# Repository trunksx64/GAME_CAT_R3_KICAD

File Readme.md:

# Game//Cat ::: Revisión R3 :: Versión 3.50

## Razón de Ser e Inspiración

Este Control se basa en la Idea Original del Game//Cat Version R2, el cual a su vez se inspira en el diseño del joystick y botones del Arduino Esplora. El primer Control se implementó para ser usado como parametrizador y las siguientes revisiones se presentó como Tesis de Grado de Especialización de Instrumentación Industrial que curse. Se Utilizó principalmente como Herramienta de Programación para Tarjeta de Control de Ascensores Usando Un Firmware de Codito Cerrado. Se Implementó FREERTOS para su uso, así como librerías Básicas en MPLABX y XC16. La idea principal es utilizar los Microcontroladores de 16Bits de Microchip con periféricos listos y configurados. Es pequeño y Portable, ideal para llevar a todo lado, no intenta competir con controles similares a Arduino. Se desea implementar a futuro un Bootloader tanto por USB, RS232, SD y CAN.

Inicialmente, se Requiere un Programador Basado en PICKIT2/ICD3, MPLAB C30 Y MPLAB V4.0 como mínimo. 

En la Actualidad se recomienda el MPLAB SNAP, XC16 y MPLABX V6.0 

Algunos Elementos "Footprints" y "Symbols" están basados en mis librerías, cuáles encontrarán en este mismo Repositorio.

## Características del Hardware

  * Microcontrolador PIC24HJ128GP504.
  * Pantalla LCD PCD8544 (Based Nokia GLCD) - SPI.
  * Joystick Análogo de 2 ejes + Botón Digital.
  * 4 Botones Digitales.
  * Accelerometro - MMA8452Q - I2C. 
  * Sensor de Temperatura (LM61).
  * Sensor de Luz (LDR).
  * Memoria Eeprom 24LCXXX - I2C.
  * Memoria Ram 23KXX - SPI.
  * Ranura Memoria Micro-SD - SPI.
  * Buzzer por PWM.
  * Conexión USB - FTDI-RL232/UART - 5V.
  * Conexión CAN 5V.
  * 2 LED´s de Actividad.
  * Salidas Para PWM y UART - Con figurables - 3.3V.
  * Conexión ICSP con línea AUX, para control extra de puerto.
  * Cargador de Batería Lipo (MCP73831) con Indicador LED.

## Características Específicas

  * Debido a que el PIC trabaja a 3.3V, el uso del PCA82C251 y el FTDI-RL232 está a 5V, alimentado directamente por el Control USB, el FTDI-RL232 se encarga de "gestionar" la alimentación del sistema proporcionando un arranque suave en la tensión, luego se pasa por un regulador de 3,3V para alimentar el resto de componentes.
  * Para Potabilidad he agregado un control para la carga de Baterías de tipo Lipo, este gobernado él con el CI MCP73831, el cual mediante el uso del Mosfet DMP1045, intercambia la alimentación proveniente del FTDI-RL232 y la Batería según el estado de conexión USB, se puede usar Baterías de 3,7V en adelante hasta un máximo de 6V, cuando el Game//Cat está usando la Batería, el FTDI-RL232 se deshabilita.
  * Para el Manejo del Joystick, Botones, Sensor de Temperatura y Luz. He empleado el CI-74HC4051, que es un Multiplexor Análogo para leer los Valores por el módulo ADC, el cual puede utilizarse de 10 o 12Bits en conjunto con un canal DMA si fuere necesario.
  * La Comunicación UART, es una Salida/Entrada dedicada con un conversor de tensión de 3.3V a 5V de forma bidireccional con transistores Mosfet, con el fin de proteger y poder comunicar el PIC24H con cualquier tipo de dispositivo.
  * La Comunicación USB se hace por medio del CI FTDI-RL232, esto es porque el PIC no posee dicho Módulo y además permite ahorrar en la Memoria del PIC el Stack del USB, esto permite que sea Conectar y Usar, puesto que los Drives de este USB son reconocidos de forma inmediata por Windows y Linux sin problemas.
  * La Comunicación CAN la he Incluido porque en estos momentos trabajo con esta interfase y su popularidad ha crecido bastante, por experiencia este BUS es muy robusto y fácil de usar, en el PIC se hace uso de dos canales DMA teniendo una respuesta bastante rápida y sin sacrificar la memoria RAM principal, su conexión se hace por medio del Transeiver PCA82C251, además he agregado un par de diodos TVH para proteger dicho CI.
  * La Ranura para la Tarjeta Micro-SD, posee conexión con el Módulo SPI, el cual está compartida con la Memoria Ram 23Kxxx, Además la pantalla posee también una conexión al segundo Módulo SPI, que puede usarse para "colgar" otros dispositivos si no vamos a usar la Pantalla.
  * El control del Buzzer se ha dejado por un Pin que puede ser utilizado tanto por el módulo PWM o un pin Común, su uso dependerá del Programa o Aplicación.
  * Posee una Memoria I2C en conjunto con un Accelerometro, con comunicación directa.
  * La programación se hace por medio de la conexión ICSP o Bootloader por USB, usando cualquier programador, PICKIT2-3 y/ó ICD2-3, igual estas salidas pueden usarse como cualquier puerto, teniendo presente que no poseen ninguna protección a tensiones superiores de 3,3V.
  * Ya por Último, he dejado dos visualiza-dores, que son libres de uso.

Básicamente, esto es el GAME//CAT, una tarjeta más que un sistema de control para usuarios avanzados, es una tarjeta de entrenamiento para los principiantes, puesto que todo lo que incluye hace uso forzoso de todo los controles que el PIC24HJ128GP504 incorpora.

## Microcontrolador

* Architecture 16-bit.
* CPU Speed Max. 40 MIPS.
* Memory Type Flash.
* Program Memory 128Kb.
* RAM 8,192 Bytes.
* Temperature Range C -40 to 150.
* Operating Voltage Range (V) 3 to 3.6.
* I/O Pins 35 & Pin Count 44.
* Internal Oscillator 7.37 MHz, 32.768 kH.
* Digital Communication Peripherals 2-UART, 2-SPI,1-I2C, 1-CAN.
* Comparators 2, Capture/Compare/PWM Peripherals 4/4, PWM Resolution bits 16.
* Timers 5 x 16-bit 2 x 32-bit.
* Parallel Port PMP(No Usado), Hardware RTCC-1 (No Usado).
* Chanel DMA-8.
* Cap Touch Channels-13 (No Usado).

## Versiones

* 2017 : 1.0.0 : Primera Versión en Kicad 4
* 2017 : 1.2.0 : Se Agregó Conversión de Tensión 5V a 3.3V Bidireccional en salida UART y PWM, se eliminó conexión DC externa.
* 2018 : 2.0.0 : Se Migró completamente a Kicad 5, el Led control se removió para dar opción de selección de Periférico SPI (Ram y SD).
* 2018 : 2.1.0 : Se rediseñó y corrigió error en botón del Joystick, se corrigió el trucado de líneas de Programación PGM y PGD.
* 2018 : 2.2.0 : Se Agregó Resistencias de protección (0Ohm) en entradas Jack RJ11 de Programación.
* 2018 : 2.1.0 : Se Agregó y Calibro Resistencia del Botón de Reset, se agregó control se Carga para Bateria Lipo 3.3V.
* 2018 : 2.5.0 : Se Actulizaron Logos de la Marca y de Hardware Libre, se Actualizó a licencia Creative Commons V4.
* 2018 : 2.7.0 : Se Actualizaron las Librerías de Módulos de Kicad, basadas en Progetti Walter.
* 2018 : 2.9.0 : Se Agregaron condensadores de filtrado al multiplexor análogo, se cambiaron los botones por diseño con poste.
* 2019 : 2.9.1 : Se Organizaron los Archivos para Hospedarlos en Github, Se Ordenaron condensadores y Cristal del PIC.
* 2021 : 2.9.1 : Se Actualiza a KiCad 6 todos los archivos y Librerías.
* 2022 : 3.0.0 : Se Actualizaron los Valores de las resistencias del conversor de 5V-3.3V de un 1K a 10K.
* 2022 : 3.1.0 : Se reestructuró completamente los esquemáticos y se usaron páginas separadas para cada Módulo.
* 2022 : 3.2.0 : Se corrigieron errores en los anchos de pista y reubicaron varios elementos como Seregrafia.
* 2022 : 3.3.0 : Se Actualizaron los conectores Moles para cuatros Salidas, sumando VCC y GND para alimentar controles externos.
* 2022 : 3.5.0 : Se Actualizaron los Logos y posiciones de Seregrafia de Varios componentes.

## ERRATAS

* Debido a tolerancia de tensión del MCP2551, no es posible usarlo para tensiones de 3.3V, cuál hacer imposible usar el CANBUS, sé recomienda usar el PCA82C251 cuál soportar desde 1.8V hasta 24V.

## Créditos

xDNA Electronics & Desing es una microempresa Personal, que se dedica y encarga de elaborar proyectos de Control y Automatización por pedido, su idea es colaborar y ayudar a quines a si lo requieran, el proyecto se hizo principalmente como Hobby el cual gracias a terceros se pudo implementar y hacer su creación, por lo cual se da la libertad de usarlo para experimentar sin hacer uso comercial del mismo.

## Licencia

Licensed under Attribution-NonCommercial-ShareAlike 4.0 International (CC BY-NC-SA 4.0)

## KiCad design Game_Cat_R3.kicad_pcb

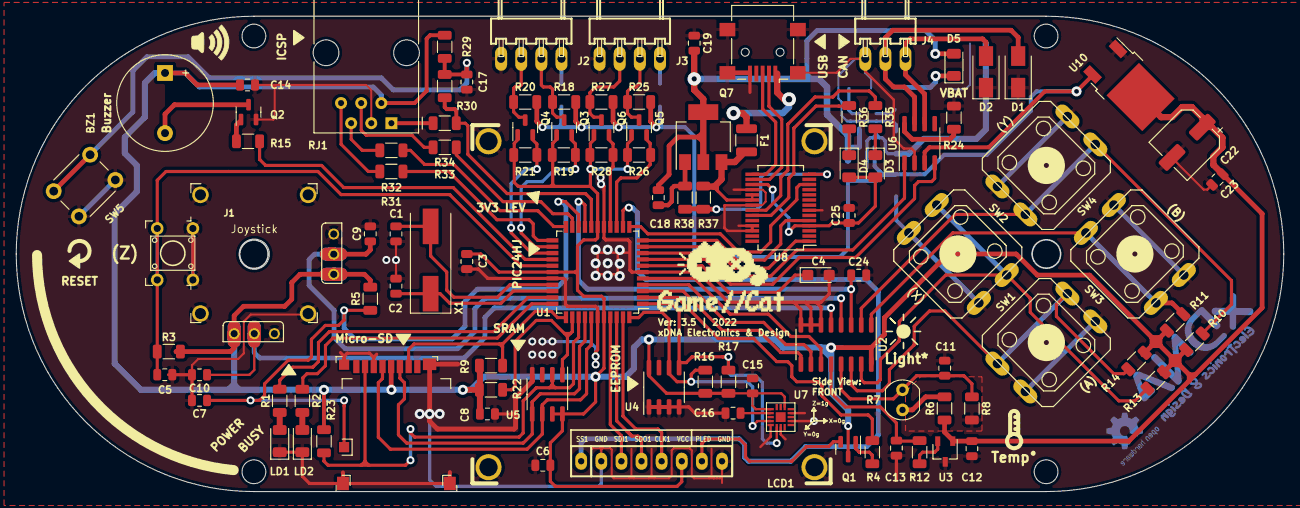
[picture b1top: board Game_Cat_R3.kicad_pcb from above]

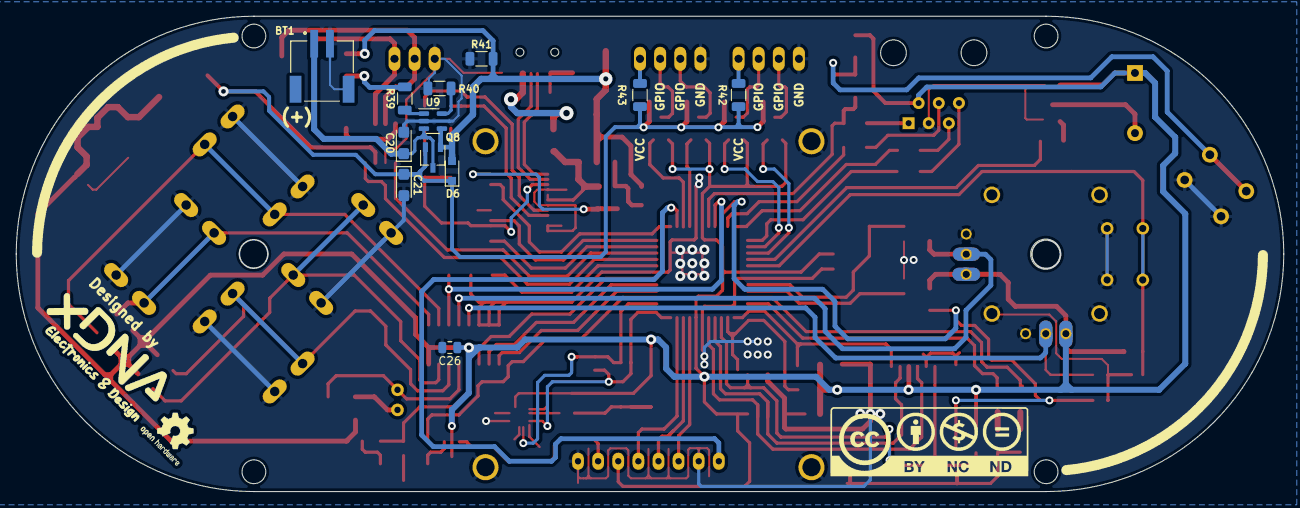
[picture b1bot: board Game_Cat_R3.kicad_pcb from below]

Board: 2 copper layers, 160.0 x 60.0 mm, 113 parts (12 on the bottom side), 87 nets.

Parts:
BT1: 3V7; Connector_1x02_P2.0mm
BZ1: Buzzer; Buzzer_12x9.5RM7.6
C1, C2: 22pF; C_0805_2012Metric
C3, C25: 100uF; C_0805_2012Metric
C4: 10uF; CP_EIA-3216-18_Kemet-A
C5, C7, C9, C10, C24, C26: 10pF; C_0805_2012Metric
C6, C8, C11, C12, C14, C15, C16: 10nF; C_0805_2012Metric
C13, C17, C18, C19, C23: 100nF; C_0805_2012Metric
C20: 4.7uF; CP_EIA-3216-18_Kemet-A
C21: 1uF; CP_EIA-3216-18_Kemet-A
C22: 100uF; CP_Elec_6.3x4.5
D1, D2: D_TVS; D_SMA
D3, D4: LED; LED_1206_3216Metric
D5: VBAT; LED_1206_3216Metric
D6: BAT60J; D_SOD-323_HandSoldering
F1: Fuse; R_1210_3225Metric
J1: Joystick; JOYSTICK_TUMB
J2: UART; MOLEX_KK_1x04_P2.54mm_HORIZONTAL
J3: PWM; MOLEX_KK_1x04_P2.54mm_HORIZONTAL
J4: CAN; MOLEX_KK_1x03_P2.54mm_HORIZONTAL
LCD1: PCD8544-BASE; GLCD_PCD8544_BASE
LD1: POWER; LED_1206_3216Metric
LD2: BUSY; LED_1206_3216Metric
Q1: MMBT3906; SOT-23
Q2: MMBT3904; SOT-23
Q3, Q4, Q5, Q6: BSS138; SOT-23
Q7: IRFL901; SOT-223
Q8: NTR1P02LT1G; TSOT-23
R1, R2, R35: 330R; R_1206_3216Metric
R3, R4, R5, R6, R8, R10, R11, R12, R13, R14, R18, R19, R20, R21, R25, R27, R28, R29, R37, R40: 10K; R_1206_3216Metric
R7: VT93xx; R_LDR_4.9x4.2mm_P2.54mm_Vertical
R9, R15, R22, R23, R24, R26, R38, R42, R43: 1K; R_1206_3216Metric
R16, R17: 4K7; R_1206_3216Metric
R30, R39: 470R; R_1206_3216Metric
R31, R32, R33, R34: 0R; R_1206_3216Metric
R36: 33OR; R_1206_3216Metric
R41: 100K; R_1206_3216Metric
RJ1: RJ12; RJ12_Horizontal
Ref**: GameCatPixel; xdna_game_cat_logo_skill_pixel
SD1: Micro-SD; MICRO_SD_HC_DM3AT
SW1: (A); SW_PUSH_PTS_125x12mm_SNAP_GREEN
SW2: (X); SW_PUSH_PTS_125x12mm_SNAP_BLUE
SW3: (B); SW_PUSH_PTS_125x12mm_SNAP_RED
SW4: (Y); SW_PUSH_PTS_125x12mm_SNAP_YELLOW
SW5: RESET; SW_PUSH_6mm_H5mm
U1: PIC24HJXXXGPX04_TQFP; TQFP-44_10x10mm_P0.8mm
U2: 74HC4051; SOIC-16_3.9x9.9mm_P1.27mm
U3: LM61; TSOT-23
U4: M24C512; SOIC-8_3.9x4.9mm_P1.27mm
U5: 23KXX; SOIC-8_3.9x4.9mm_P1.27mm
U6: PCA82C251; SOIC-8_3.9x4.9mm_P1.27mm
U7: MMA8452Q; QFN_16_3x3x1mm_P0.5mm
U8: FT232RL; SSOP-28_5.3x10.2mm_P0.65mm
U9: MCP73831; SOT-23-5
U10: LM1117; TO-252-2
USB1: USB_B_Micro; USB_Mini-B_Lumberg_2486_01_Horizontal
X1: 4Mhz; Crystal_SMD_HC49-SD

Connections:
+3.3VA: D3.2 (A), D4.2 (A), U8.4 (VCCIO), U8.17 (3V3OUT)
+3V3: BZ1.1 (-), C3.1, C6.1, C8.1, C12.1, C14.1, C15.1, C22.1, C23.2, C26.1, J1.1 (V+), J1.4 (H+~), LCD1.6 (VCC), Q1.3 (C), Q3.1 (G), Q4.1 (G), Q5.1 (G), Q6.1 (G), R3.2, R5.2, R6.1, R9.1, R10.1, R11.1, R13.1, R14.1, R16.1, R17.1, R19.2, R21.2, R22.1, R23.1, R26.2, R28.2, R29.2, RJ1.2, SD1.4 (VDD), U1.17 (AVDD), U1.28 (VDD), U1.40 (VDD), U2.16 (VCC), U3.1 (VCC), U4.8 (VCC), U5.7 (HOLD), U5.8 (VDD), U7.1 (VDDIO), U7.14 (VDD), U10.2 (VO)
+5C: C21.1, D6.1 (K), Q8.2 (S), R18.1, R20.1, R25.1, R27.1, R42.1, R43.1, U6.3 (VCC), U10.3 (VI)
+5V: F1.2, Q7.3 (S), R37.2, U8.19 (~RESET), U8.20 (VCC)
/BUTTONS/Axis(X): C10.1, J1.2 (V), U2.5 (A5)
/BUTTONS/Axis(Y): C9.1, J1.5 (H), U2.4 (A7)
/BUTTONS/Button(A): R14.2, SW1.1, SW1.2, U2.14 (A1)
/BUTTONS/Button(B): R11.2, SW3.1, SW3.2, U2.1 (A4)
/BUTTONS/Button(X): R13.2, SW2.1, SW2.2, U2.15 (A2)
/BUTTONS/Button(Y): R10.2, SW4.1, SW4.2, U2.2 (A6)
/BUTTONS/CANH: D1.2 (A2), J4.2, U6.7 (CAN+)
/BUTTONS/CANL: D2.2 (A2), J4.1, U6.6 (CAN-)
/BUTTONS/Light: C11.1, R7.2, R8.1, U2.13 (A0)
/BUTTONS/Temp: C13.2, R12.1, U2.12 (A3)
/MICROCONTROLLER/VCAP: C4.1, U1.7 (VCAP)
/POWER_SUPPLY/BAT: BT1.1 (+), C20.1, Q8.3 (D), U9.3 (VBAT)
/POWER_SUPPLY/CBUS0: R36.1, U8.23 (CBUS0)
/POWER_SUPPLY/CBUS1: R35.1, U8.22 (CBUS1)
/POWER_SUPPLY/PWREN: R37.1, R38.2, U8.14 (CBUS3)
ADC-IN: C24.1, U1.19 (RA0/CN2/VREF+/AN0), U2.3 (A)
AUX_ICD: R31.2, U1.23 (AN4/C1IN-/RP2/CN6/RB2)
BUTTON_Z: C5.1, J1.7 (B+), R3.1, U1.27 (RC2/CN10/PMA2/RP18/CVREF/AN8)
BUZZER: R15.1, U1.26 (RC1/CN9/RP17/AN7)
CHECK-SD: C7.1, R5.1, U1.20 (RA1/CN3/VREF-/AN1)
GLCD_LED: R4.1, U1.2 (RC6/PMA1/CN18/RP22)
GND: BT1.2 (-), C1.2, C2.1, C3.2, C4.2, C5.2, C6.2, C7.2, C8.2, C9.2, C10.2, C11.2, C12.2, C13.1, C14.2, C15.2, C16.2, C17.1, C19.1, C20.2, C21.2, C22.2, C23.1, C24.2, C25.2, C26.2, D1.1 (A1), D2.1 (A1), J1.3 (V-), J1.6 (H-), J1.8 (B-), J1.9 (SHIELD), J2.4, J3.4, J4.3, LCD1.2 (SCE), LCD1.8 (GND), LD1.1 (K), LD2.1 (K), Q2.2 (E), R8.2, R24.1, R40.1, R41.1, RJ1.3, SD1.6 (VSS), SW1.3 (K), SW1.4 (A), SW2.3 (K), SW2.4 (A), SW3.3 (K), SW3.4 (A), SW4.3 (K), SW4.4 (A), SW5.1, U1.6 (VSS), U1.16 (AVSS), U1.29 (VSS), U1.39 (VSS), U2.6 (~E), U2.7 (VEE), U2.8 (GND), U3.3 (GND), U4.1 (E0), U4.2 (E1), U4.3 (E2), U4.4 (VSS), U4.7 (~WC), U5.4 (VSS), U6.2 (GND), U7.5 (GND), U7.7 (SAO), U7.10 (GND), U7.12 (GND), U8.7 (GND), U8.18 (GND), U8.21 (GND), U8.25 (AGND), U8.26 (TEST), U9.2 (VSS), U10.1 (GND), USB1.5 (GND), USB1.6 (Shield)
I2C_SCL: R16.2, U1.44 (SCL1/RP8/CN22/PMD4/RB8), U4.6 (SCL), U7.4 (SCL)
I2C_SDA: R17.2, U1.1 (SDA1/RP9/CN21/PMD3/RB9), U4.5 (SDA), U7.6 (SDA)
MISO_GLCD: LCD1.3 (DC), U1.41 (PGED3/ASDA1/RP5/CN27/PMD7/RB5)
MISO_MEN: R23.2, SD1.7 (DO), U1.36 (RC3/PMBE/CN28/RP19), U5.2 (SO)
MOSI_GLCD: LCD1.4 (DIN), U1.42 (PGEC3/ASCL1/RP6/CN24/PMD6/RB6)
MOSI_MEN: SD1.3 (DI), U1.37 (RC4/PMA4/CN25/RP20), U5.5 (SI)
MUX_A: U1.5 (RC9/PMA6/CN19/RP25), U2.11 (S0)
MUX_B: U1.4 (RC8/PMA5/CN20/RP24), U2.10 (S1)
MUX_C: U1.3 (RC7/CN17/PMA0/RP23), U2.9 (S2)
unnamed: BZ1.2 (+), Q2.3 (C)
unnamed: C1.1, U1.30 (RA2/CN30/CLKI/OSC1), X1.2
unnamed: C2.2, U1.31 (RA3/CN29/CLKO/OSC2), X1.1
unnamed: C16.1, U7.2 (BYP)
unnamed: C17.2, R29.1, R30.1, SW5.2
unnamed: C18.1, C19.2, D5.2 (A), D6.2 (A), Q7.2 (D), Q8.1 (G), R41.2, U9.4 (VDD)
unnamed: C18.2, Q7.1 (G), R38.1
unnamed: D3.1 (K), R35.2
unnamed: D4.1 (K), R36.2
unnamed: D5.1 (K), R39.2
unnamed: F1.1, USB1.1 (VBUS)
unnamed: J2.1, R42.2
unnamed: J2.2, Q3.3 (D), R18.2
unnamed: J2.3, Q4.3 (D), R20.2
unnamed: J3.1, R43.2
unnamed: J3.2, Q5.3 (D), R25.2
unnamed: J3.3, Q6.3 (D), R27.2
unnamed: LCD1.7 (LED), Q1.2 (E)
unnamed: LD1.2 (A), R1.2
unnamed: LD2.2 (A), R2.2
unnamed: Q1.1 (B), R4.2
unnamed: Q2.1 (B), R15.2
unnamed: R1.1, U1.32 (RA8/PMA8/TDO)
unnamed: R2.1, U1.33 (SOSCI/RP4/CN1/RB4)
unnamed: R6.2, R7.1
unnamed: R12.2, U3.2 (Vo)
unnamed: R24.2, U6.8 (Rsl)
unnamed: R31.1, RJ1.6
unnamed: R32.1, RJ1.5
unnamed: R33.1, RJ1.4
unnamed: R34.1, RJ1.1
unnamed: R39.1, U9.1 (STAT)
unnamed: R40.2, U9.5 (PROG)
unnamed: U8.15 (USBD+), USB1.3 (D+)
unnamed: U8.16 (USBD-), USB1.2 (D-)
PGC_ICD: R32.2, U1.22 (PGEC1/AN3/C2IN+/RP1/CN5/RB1)
PGD_ICD: R33.2, U1.21 (PGED1/AN2/C2IN-/RP0/CN4/RB0)
RESET_CTRL: R30.2, R34.2, U1.18 (MCLR)
RX_CAN: U1.8 (PGED2/EMCD2/RP10/CN16/PMD2/RB10), U6.4 (RxD)
RX_UART_A: Q4.2 (S), R21.1, U1.25 (RC0/CN8/RP16/AN6)
RX_UART_B: Q6.2 (S), R28.1, U1.15 (AN9/RP15/CN11/PMCS1/RB15)
RX_USB: U1.10 (AN12/RP12/CN14/PMD0/RB12), U8.1 (TXD)
SCK_GLCD: LCD1.5 (CLK), U1.43 (INT0/RP7/CN23/PMD5/RB7)
SCK_MEM: SD1.5 (SCLK), U1.38 (RC5/PMA3/CN26/RP21), U5.6 (SCK)
SLEEP_USB: U1.12 (RA10/PMA10/TMS), U8.12 (CBUS4)
SS_GLCD: LCD1.1 (RES), U1.13 (RA7/PMA7/TCK)
SS_RAM: R22.2, U1.35 (RA9/PMA9/TDI), U5.1 (CS)
SS_USD: R9.2, SD1.2 (CS), U1.34 (RA4/CN0/T1CK/SOSCO)
TX_CAN: U1.9 (PGEC2/RP11/CN15/PMD1/RB11), U6.1 (TxD)
TX_UART_A: Q3.2 (S), R19.1, U1.24 (AN5/C1IN+/RP3/CN7/RB3)
TX_UART_B: Q5.2 (S), R26.1, U1.14 (AN10/RTCC/RP14/CN12/PMWR/RB14)
TX_USB: U1.11 (AN11/RP13/CN13/PMRD/RB13), U8.5 (RXD)

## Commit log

2022-11-27 26/11/22/A
2022-12-21 21/12/22/A
2023-03-25 24/03/23/A
2023-12-26 26/12/13/A
2024-06-08 08/06/24/A
